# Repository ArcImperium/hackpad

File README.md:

# Hackpad
My personal macropad with 9 keys. There is also a mini led that indicates status.

I made this for Hack Club's Blueprint.

# Parts
- PCB (1)
- Seeed XIAO RP2040 (1)
- MX-Style Switches (9)
- Blank DSA Keycaps (9)
- SK6812 MINI-E LED (1)
- M3x16mm Screws (4)
- M3x5mx4mm Heatset Inserts (4)
- 3d Printed Case (1)

# Hardware
The macropad uses a 90mm x 61mm PCB board.
I used KiCAD to design the PCB.
It includes a Seeed Studio XIAO RP2040 as the micrcontroller, 9 switches for keys, and a mini led.
Each key is wired to its own pin on the XIAO, and they all connect to ground.

# Case
The case for the macropad was made using Onshape.
The stylish design is a box with filleted edges.
It includes a base as well as a cover to fit the PCB.
It can also be held together by screws in each corner.

# Software
The macropad uses kmk firmware, which is Python-based and found at https://github.com/KMKfw/kmk_firmware/blob/main/docs/en/Getting_Started.md.
The XIAO also needs circuitpython to be fully compatible.

For assembly, download circuitpython to the XIAO drive, then upload the kmk file and main.py to the board.

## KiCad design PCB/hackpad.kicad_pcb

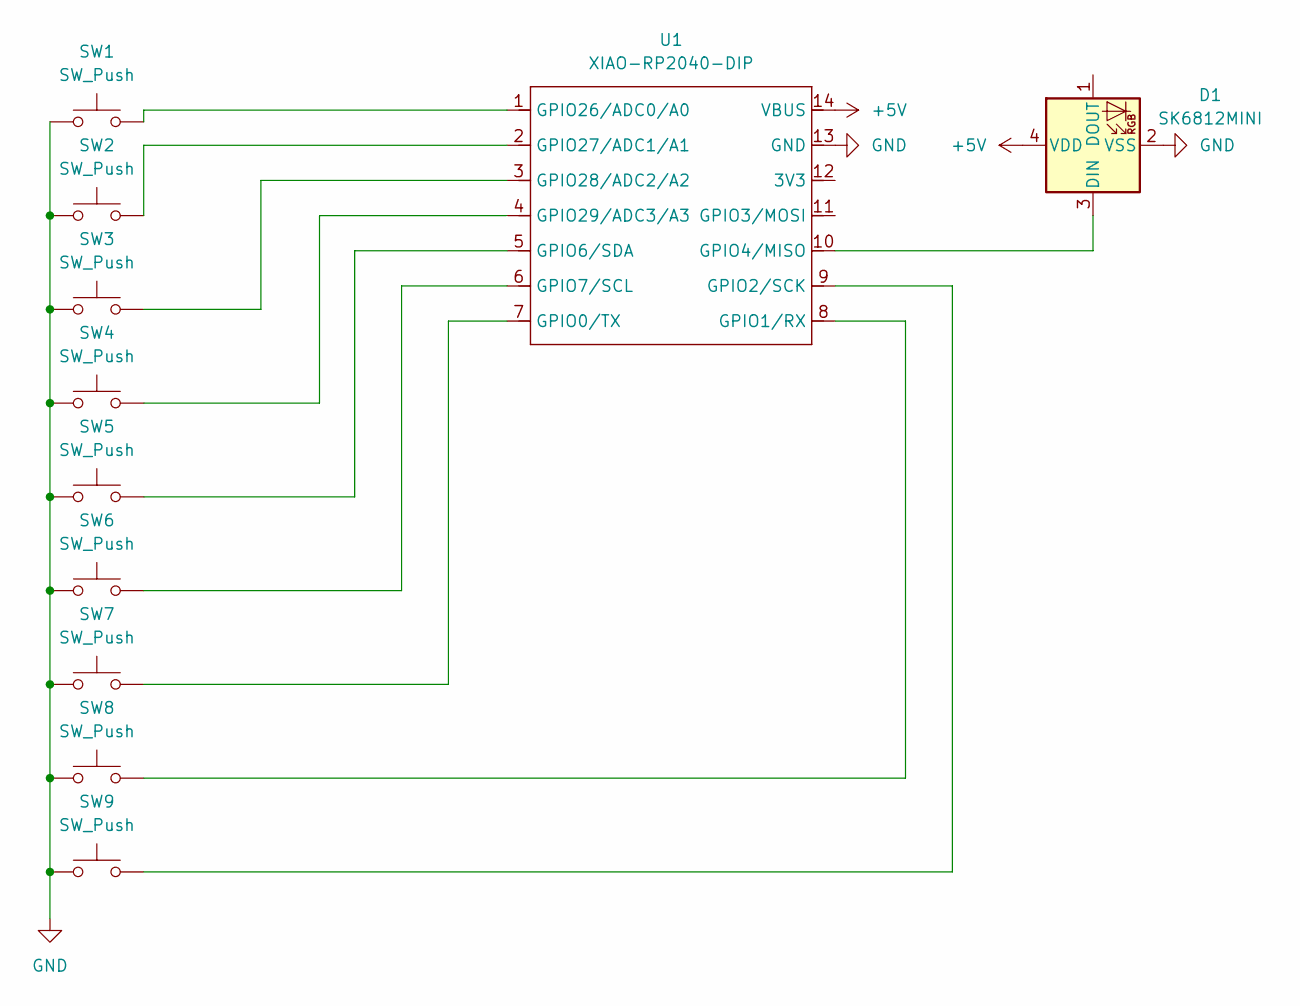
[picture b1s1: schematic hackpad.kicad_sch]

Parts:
D1: SK6812MINI; MX_SK6812MINI-E_REV
SW1, SW2, SW3, SW4, SW5, SW6, SW7, SW8, SW9: SW_Push; SW_Cherry_MX_1.00u_PCB
U1: XIAO-RP2040-DIP

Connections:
+5V: D1.4 (VDD), U1.14 (VBUS)
GND: D1.2 (VSS), SW1.1, SW2.1, SW3.1, SW4.1, SW5.1, SW6.1, SW7.1, SW8.1, SW9.1, U1.13 (GND)
unnamed: D1.3 (DIN), U1.10 (GPIO4/MISO)
unnamed: SW7.2, U1.7 (GPIO0/TX)
unnamed: SW8.2, U1.8 (GPIO1/RX)
unnamed: SW9.2, U1.9 (GPIO2/SCK)
unnamed: SW5.2, U1.5 (GPIO6/SDA)
unnamed: SW6.2, U1.6 (GPIO7/SCL)
unnamed: SW1.2, U1.1 (GPIO26/ADC0/A0)
unnamed: SW2.2, U1.2 (GPIO27/ADC1/A1)
unnamed: SW3.2, U1.3 (GPIO28/ADC2/A2)
unnamed: SW4.2, U1.4 (GPIO29/ADC3/A3)

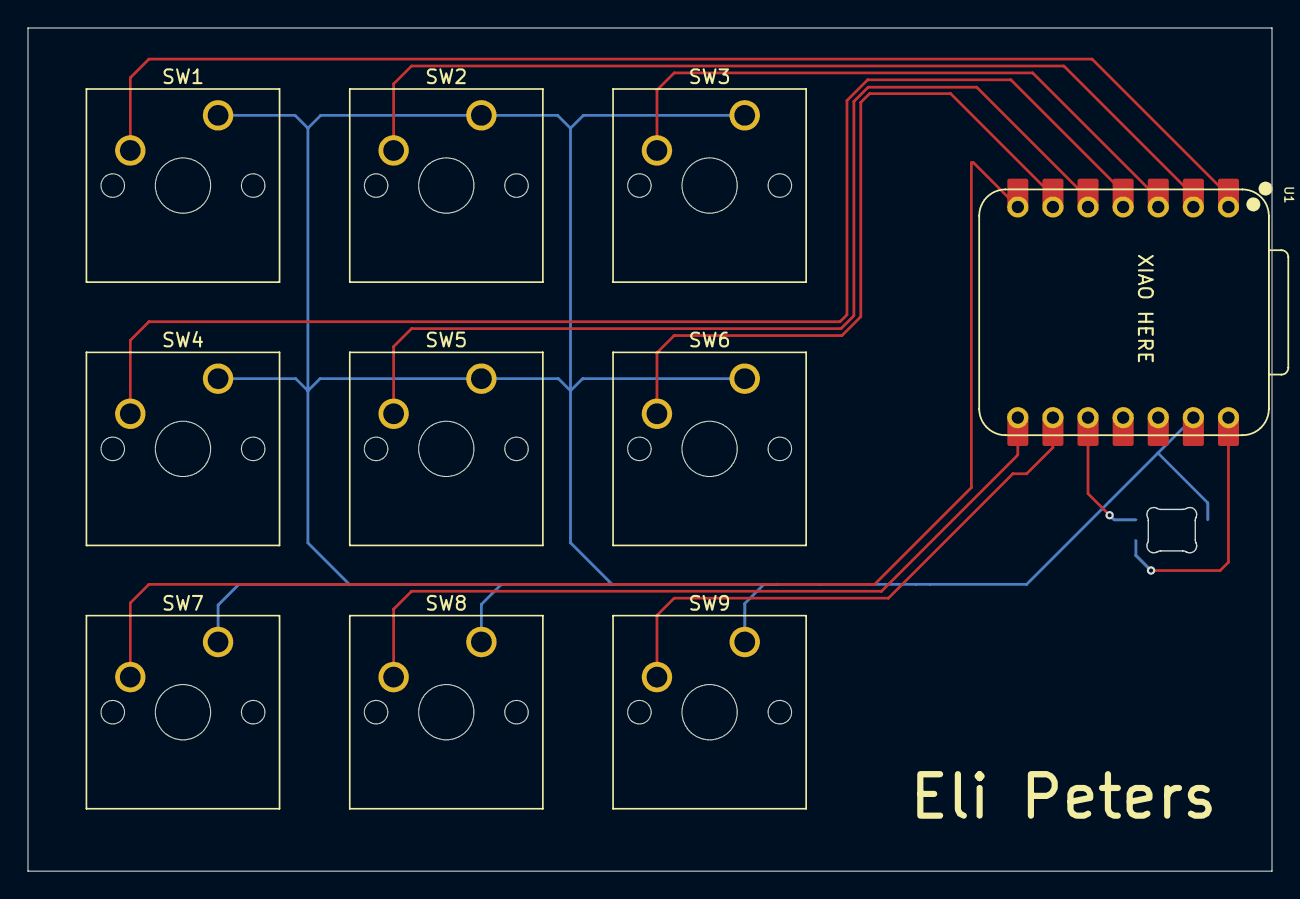
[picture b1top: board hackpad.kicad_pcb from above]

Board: 2 copper layers, 90.0 x 61.0 mm, 11 parts (0 on the bottom side), 12 nets.

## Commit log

2026-01-30 Please Read Me
2026-01-30 Screenshots
2026-01-30 Fixed Screenshots
2026-01-30 Submitting Hackpad
2026-01-31 Updated PCB
2026-01-31 Rewired LED on PCB
2026-02-01 Fixed Screenshots for LED Footprint
2026-02-01 Fixed LED Footprint
